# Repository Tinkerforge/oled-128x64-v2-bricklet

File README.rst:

OLED 128x64 Bricklet 2.0
========================

This repository contains the firmware source code and the hardware design
files. The documentation generator configs can be found at
https://github.com/Tinkerforge/generators

Repository Content
------------------

software/:
 * examples/: Examples for all supported languages
 * build/: Compiled files
 * src/: Source code of firmware
 * Makefile: Makefile to build project

hardware/:
 * Contains KiCad project files and additionally schematics as PDF

datasheets/:
 * Contains datasheets for sensors and complex ICs that are used

Hardware
--------

The hardware is designed with the open source EDA Suite KiCad
(http://www.kicad.org). Before you are able to open the files,
you have to install the Tinkerforge kicad-libraries
(https://github.com/Tinkerforge/kicad-libraries). You can either clone
them directly in hardware/ or clone them in a separate folder and
symlink them into hardware/
(ln -s kicad_path/kicad-libraries project_path/hardware). After that you
can open the .pro file in hardware/ with KiCad and from there view and
modify the schematics and the PCB layout.

Software
--------

If you want to do your own Brick/Bricklet firmware development we highly
recommend that you use our build environment setup script and read the
tutorial (https://www.tinkerforge.com/en/doc/Tutorials/Tutorial_Build_Environment/Tutorial.html).

To compile the C code we recommend you to install the newest GNU Arm Embedded
Toolchain (https://launchpad.net/gcc-arm-embedded/+download).
You also need to install bricklib2 (https://github.com/Tinkerforge/bricklib2).

You can either clone it directly in software/src/ or clone it in a
separate folder and symlink it into software/src/
(ln -s bricklib_path/bricklib2 project_path/software/src/). Finally make sure to
have CMake installed (http://www.cmake.org/cmake/resources/software.html).

After that you can build the firmware by invoking make in software/.
The firmware (.zbin) can then be found in software/build/ and uploaded
with brickv (click button "Flashing" on start screen).

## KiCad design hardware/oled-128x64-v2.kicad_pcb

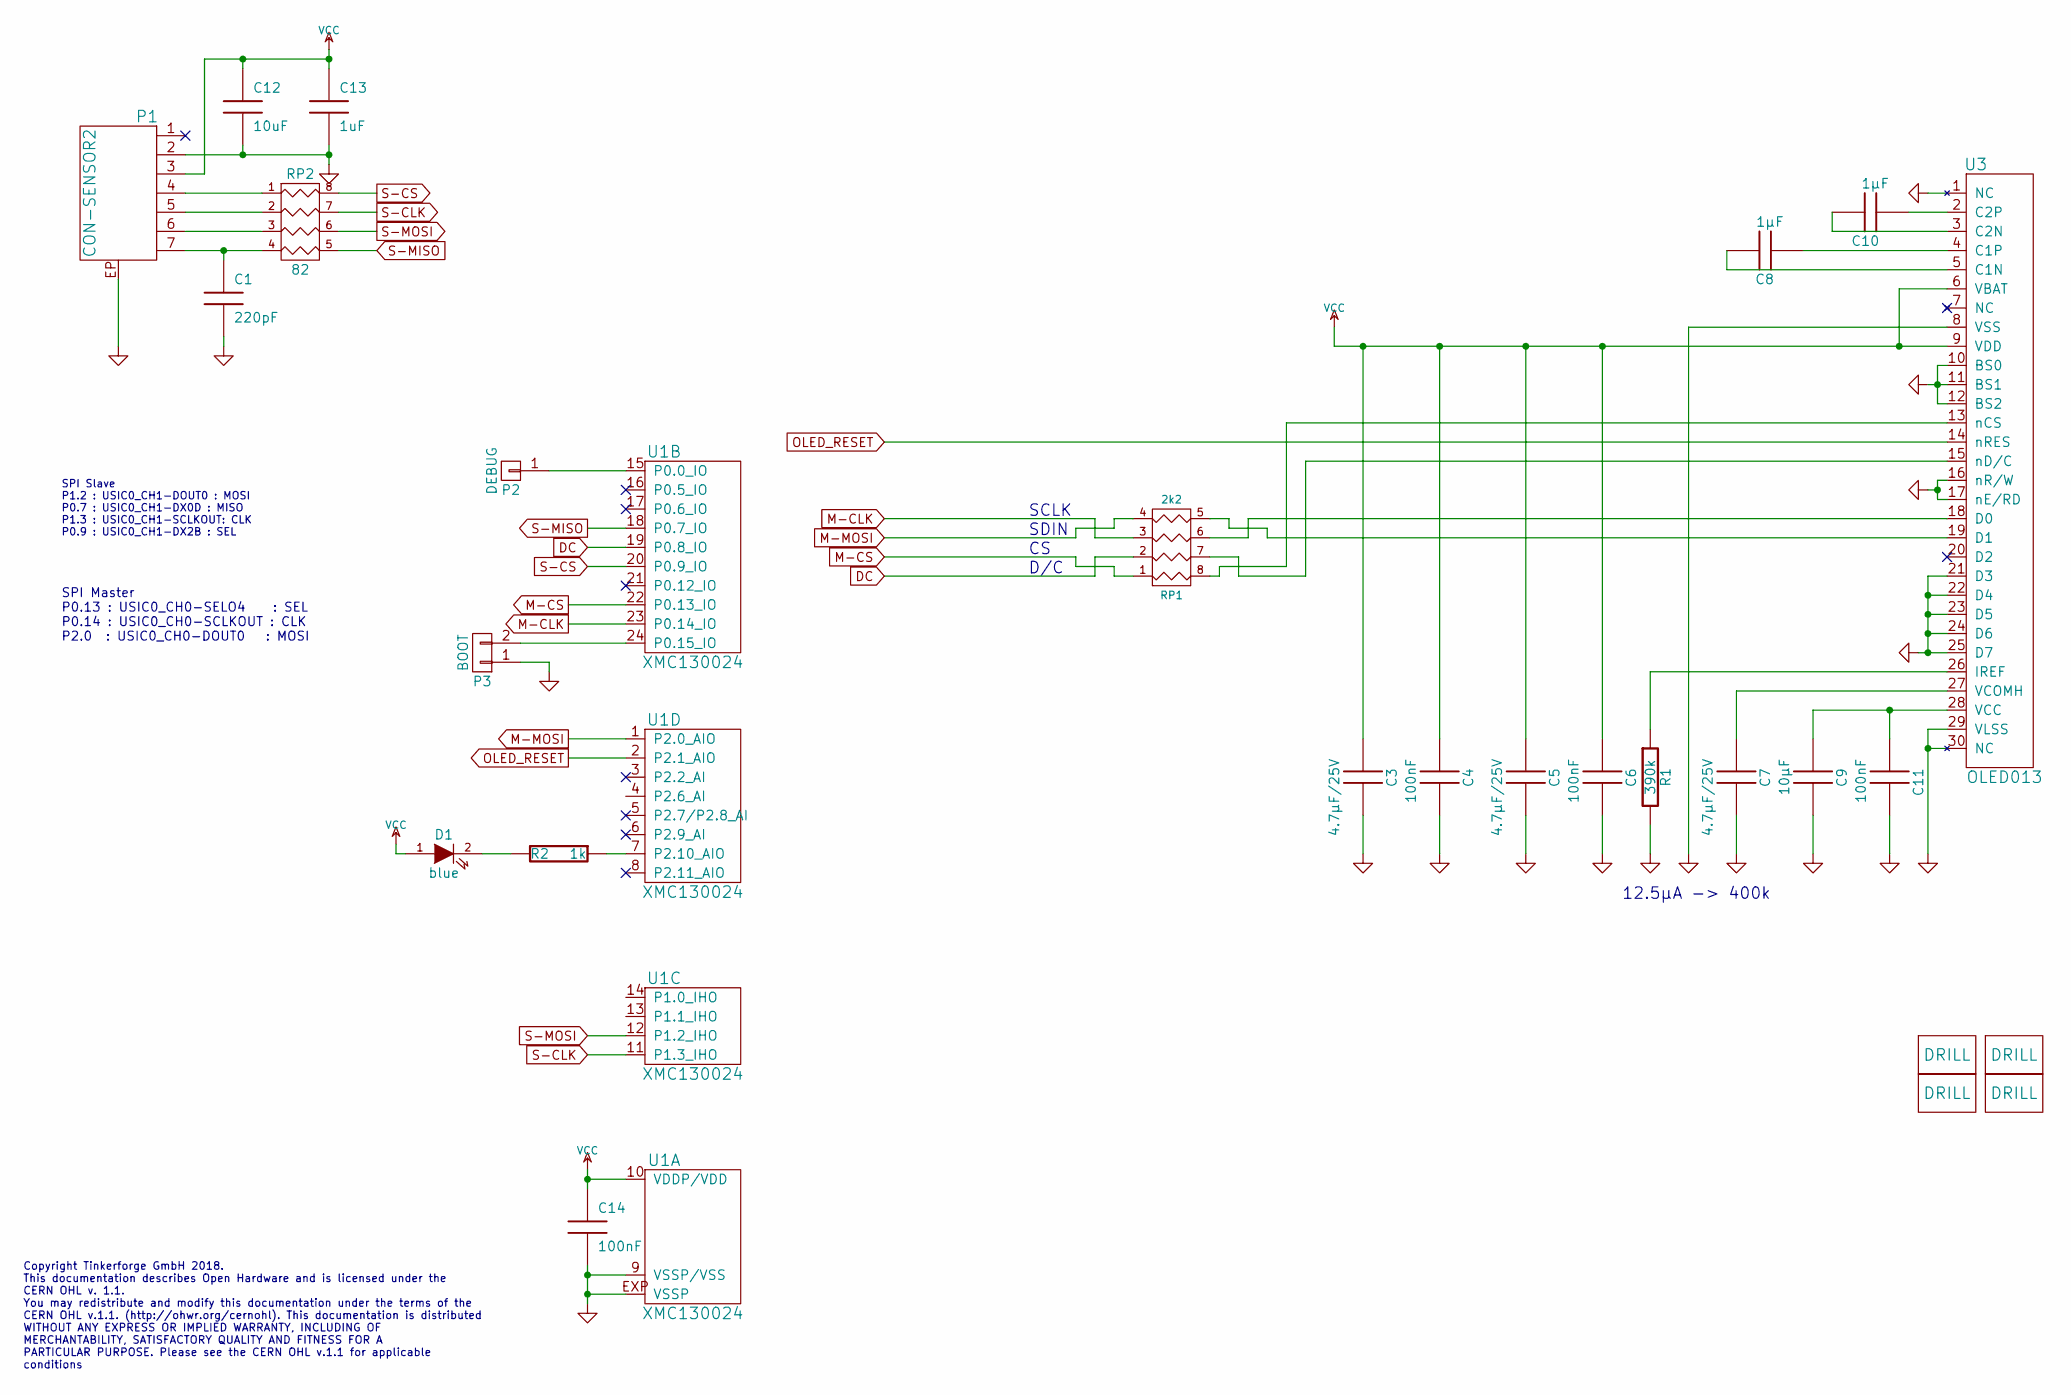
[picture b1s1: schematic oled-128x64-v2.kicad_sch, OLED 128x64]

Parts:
C1: 220pF; C0402F
C3, C5, C7: 4.7µF/25V; C0805
C4, C6, C11, C14: 100nF; C0603F
C8, C10: 1µF; C0603F
C9: 10µF; C0805
C12: 10uF; C0805
C13: 1uF; C0603F
D1: blue; D0603F
P1: CON-SENSOR2
P2: DEBUG; DEBUG_PAD
P3: BOOT; SolderJumper
R1: 390k; R0603F
R2: 1k; R0603F
RP1: 2k2; 0603X4
RP2: 82; 4X0402
U1: XMC130024; QFN24-4x4mm-0.5mm
U3: OLED013; ER-CON30HT-1
U4, U5, U6, U7: DRILL; DRILL_NP

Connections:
DC: RP1.2, U1.19 (P0.8_IO)
GND: C1.2, C3.1, C4.1, C5.1, C6.1, C7.1, C9.1, C11.1, C12.2, C13.2, C14.2, P1.2, P1.EP, P3.1, R1.2, U1.9 (VSSP/VSS), U1.EXP (VSSP), U3.1 (NC), U3.8 (VSS), U3.10 (BS0), U3.11 (BS1), U3.12 (BS2), U3.16 (nR/W), U3.17 (nE/RD), U3.21 (D3), U3.22 (D4), U3.23 (D5), U3.24 (D6), U3.25 (D7), U3.29 (VLSS), U3.30 (NC)
M-CLK: RP1.3, U1.23 (P0.14_IO)
M-CS: RP1.1, U1.22 (P0.13_IO)
M-MOSI: RP1.4, U1.1 (P2.0_AIO)
unnamed: C1.1, P1.7, RP2.4
unnamed: C7.2, U3.27 (VCOMH)
unnamed: C8.1, U3.5 (C1N)
unnamed: C8.2, U3.4 (C1P)
unnamed: C10.1, U3.3 (C2N)
unnamed: C10.2, U3.2 (C2P)
unnamed: C9.2, C11.2, U3.28 (VCC)
unnamed: D1.2 (K), R2.2
unnamed: P1.4, RP2.1
unnamed: P1.5, RP2.2
unnamed: P1.6, RP2.3
unnamed: P2.1, U1.15 (P0.0_IO)
unnamed: P3.2, U1.24 (P0.15_IO)
unnamed: R1.1, U3.26 (IREF)
unnamed: R2.1, U1.7 (P2.10_AIO)
unnamed: RP1.5 (R4), U3.19 (D1)
unnamed: RP1.6 (R3), U3.18 (D0)
unnamed: RP1.7 (R2), U3.15 (nD/C)
unnamed: RP1.8 (R1), U3.13 (nCS)
OLED_RESET: U1.2 (P2.1_AIO), U3.14 (nRES)
S-CLK: RP2.7 (R2), U1.11 (P1.3_IHO)
S-CS: RP2.8 (R1), U1.20 (P0.9_IO)
S-MISO: RP2.5 (R4), U1.18 (P0.7_IO)
S-MOSI: RP2.6 (R3), U1.12 (P1.2_IHO)
VCC: C3.2, C4.2, C5.2, C6.2, C12.1, C13.1, C14.1, D1.1 (A), P1.3, U1.10 (VDDP/VDD), U3.6 (VBAT), U3.9 (VDD)

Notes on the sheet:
SPI Slave P1.2 : USIC0_CH1-DOUT0 : MOSI P0.7 : USIC0_CH1-DX0D : MISO P1.3 : USIC0_CH1-SCLKOUT: CLK P0.9 : USIC0_CH1-DX2B : SEL
Copyright Tinkerforge GmbH 2018. This documentation describes Open Hardware and is licensed under the CERN OHL v. 1.1. You may redistribute and modify this documentation under the terms of the CERN OHL v.1.1. (http://ohwr.org/cernohl). This documentation is distributed WITHOUT ANY EXPRESS OR IMPLIE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
D/C
SDIN
12.5µA -> 400k
SCLK
SPI Master P0.13 : USIC0_CH0-SELO4 : SEL P0.14 : USIC0_CH0-SCLKOUT : CLK P2.0 : USIC0_CH0-DOUT0 : MOSI

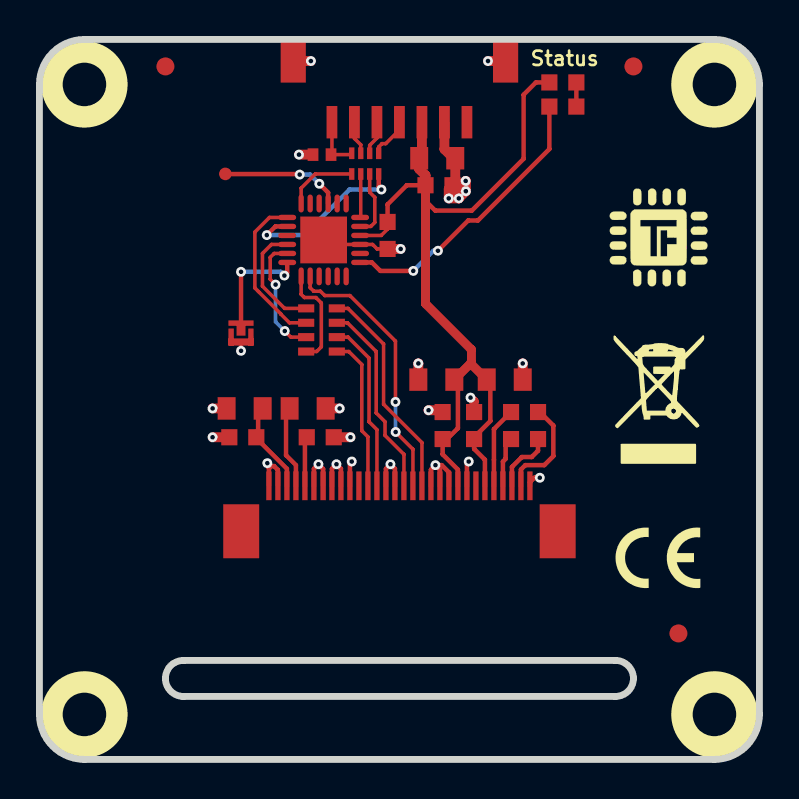
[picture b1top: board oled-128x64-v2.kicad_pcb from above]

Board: 2 copper layers, 40.0 x 40.0 mm, 31 parts (0 on the bottom side), 30 nets.

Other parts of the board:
Fiducial_Mark: VAL**; Fiducial_Mark
Fiducial_Mark#2, Fiducial_Mark#3: VAL**; Fiducial_Mark
VAL: CE_5mm

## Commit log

2018-02-16 Add datasheets
2018-02-16 Add schematic
2018-02-20 Add .gitignore
2018-02-20 Cleanup KiCad libraries config
    Ensure LibDir=kicad-libraries and LibName1=tinkerforge.
    Remove special library.
2018-02-21 Change a few pins because of the layout
2018-02-21 Add layout
2018-02-21 Fix ground plane
2018-03-13 Fix orientation of our logos
2018-03-28 Update gitignore
2018-03-28 Add initial stub version of firmware
2018-04-03 Add correct pin definitions
2018-04-04 Implement SSD1306 driver and API
2018-04-04 Use more efficient set cursor implementation
2018-04-04 Fix contrast default and maximum value
2018-04-04 Remove unused code
2018-04-04 Add simple tests
2018-05-11 Rename files
2018-06-06 set origin
2018-06-07 add text
2018-06-18 Change footprint to x0402F/x0603F
2018-06-28 Fix readme
2018-07-11 Add Makefile with docker support
2018-07-11 Update directory structure and build instructions
2018-07-11 Remove obsolete generate_makefile scripts
2018-07-31 Add 3d model (*.FCStd & *.step)
2018-07-31 Add PDF schematic
2018-09-06 Add font render script
2018-09-07 Remove off-by-4 in set_cursor function
    Where did the +=4 come from? Doesn't make any sense...
2018-09-10 Add examples
    LabVIEW example missing.
2018-09-11 Add pixel matrix and scribble example for C
2018-09-11 Add compile parameters to example
2018-09-11 Add pixel matrix and scribble examples for C#
2018-09-11 Add pixel matrix example for Delphi
2018-09-12 Add pixel matrix and scribble examples for java
2018-09-12 Add pixel matrix and scribble example for JavaScript
2018-09-12 Add pixel matrix example for MATLAB/Octave
2018-09-12 Add pixel matrix and scribble examples for perl
2018-09-12 Add pixel matrix and scribble example for PHP
2018-09-12 Add load image, pixel matrix and scribble example for Python
2018-09-12 Add pixel matrix and scribble example for Ruby
2018-09-12 Add pixel matrix example for Shell
2018-09-12 Add pixel matrix and scribble example for VB.NET
2018-09-28 Add LabVIEW hello world example
2018-10-02 Add BOOTLOADER_FIX_POINTER_END define
2018-10-04 Add rev to changelog
2018-10-16 Remove in-development marker
2018-11-06 Add rust examples
2018-11-07 rust: Accept host names for ip connection, fix naming inconsistencies
2018-11-30 Fix drawing race-condition
2018-11-30 Add v2.0.1 entry to changelog
2018-11-30 Make sure display is initialized as blank screen
2018-11-30 Add ref for v2.0.2
2018-12-14 Add go examples.
2018-12-18 go: Change import path.
2018-12-18 go: Change import path again.
2018-12-20 rust: Reformat examples.
2019-01-24 mqtt: Add examples.
2019-01-24 mqtt: Fix example header.
2019-01-24 mqtt: Remove executable bit in example permissions.
2019-01-24 go: Minor example fixes.
2019-01-24 mqtt: Minor example fixes.
2019-03-05 Fix drawing race condition in automatic-draw mode
2019-03-05 Add ref for 2.0.3
2019-05-28 Improve SPI IRQ performance
    Use local pointer to save the time for accessing the struct
2019-05-29 Increase version for new release (changes in bricklib2)
2019-08-13 Add updated font editor
2019-08-19 Make clear-display obey the automatic-draw config
2019-08-19 Add commit ref to changelog
2020-01-13 examples: Use python3 input instead of python2 raw_input.
2020-01-13 examples: mqtt: Remove trailing whitespace.
2020-01-14 examples: Use python3 input by default.
2020-02-26 examples: Update "Change UID" comment style
2020-02-26 examples: Whitespace
2020-03-16 Whitespace
2020-04-07 examples: rust: Always block when calling bindings functions.
2020-08-19 Add uc examples.
2020-08-25 uc: Fix whitespace
2020-08-27 uc: Fix warnings.
2020-09-02 uc: Add example driver note.
2021-10-25 Update KiCad link
    https://www.kicad.org/blog/2021/10/Avoid-links-to-former-kicad-domain/
2022-03-07 Add code page 437 hint
2022-04-19 examples: uc: Rename TF_HalContext to TF_HAL.
2022-04-27 uc: Adapt to bindings changes
2022-07-06 Add license files.
2023-06-21 move to new kicad version
2024-02-23 vbnet: Fix for loop

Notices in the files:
hardware/oled-128x64-v2.kicad_pcb:
Licensed under CERN OHL v.1.1
Copyright (©) 2018, L.Lauer
